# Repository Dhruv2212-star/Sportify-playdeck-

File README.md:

# Description- this project was made for controling any media sounds via the spotify playdeck without reopening the application on your desktop  

## The main components required for this build are 
1. mechenical keyboard switches X4 
2. seeed studio XIAO RP2040 X1
3. 0.91 Inch OLED Display X1

## Final schematic should be as following- 

# Update the schematic to PCB and Route the traces 

And once the traces and connections are made, create a rectangle and make sure all the components fit insite it.
IMPORTANT- the rectangle property should be set to "edge.cuts".

# Create the case 

## Bottom case 

## top case  

# ASSEMBELED FILE
this is an model of what your project will look life later 

# you can download all the file from the 'productions' folder 
this way you would escape the trouble of recreating the PCB the case for it and you can build it yourself!!  
Now once you have the files ready, Order the PCB and 3D print the case files  
solder all the components in their places   
hot glue the pcb in the case for extra strength  
# Schematic building 
1. Add these 3 components first-
-MODULE-SEEDUINO-XIAO
-sw_push
-PinHeader_1x04_P2.54mm_Vertical
2. Connect each Sw_push to their own gpio pin, i connected them to D0, D1, D2, D3
3. connect the other part of the Sw_push to Gnd port on the Xiao RP2040  
 **That's it for your switches! now for the LCD**  
4. now on 'PinHeader_1x04_P2.54mm_Vertical' connect pin 1 to GND on the XIAO RP2040, pin2- 3.3v, pin3- D5(SCL), pin4- D4(SDA)
**That's your schematic completed!**  
# PCB tracing
1. select update to PCB
2. select the footprints for each components
3. now click on one trace of the component's pad, this will show you where it supposed to be connected, draw the lines to that region
4. now do this for all the pads present on the PCB and traces them on the PCB  
   **Thats the PCB done!**
# Case 
## Note down the dimesions from the PCB model and start with a simple sketch of a box with your dimentions and, then make the walls to fit the PCB inside then make the top case from the dimensions of the bottom case you just made and cut out the parts you need to from the top case 
# Firmware flashing 
## instal circuitpython   
1. connect your microcontroler to your PC   
2. new drive called RPI-RP2 will appear    
3. paste "adafruit-circuitpython-seeeduino_xiao_rp2040-en_US-10.2.1" file from the 'Firmware' folder given    
4. The board automatically restarts  
5. the drive is now named 'CIRCUITPY'  
6. delete any file named 'code.py' in the CIRCUITPY drive if any  
7. now copy and past these files from the firmware folder  
8. "boot.py", "code.py", entire "lib" folder  
9. yout board should look like this

CIRCUITPY/  

boot.py  

code.py  

lib/  
10. save and close the window and boot it  
# That's it! 
## open spotify and now you can control the pause, play, next, previous funtions without opening your spotify desktop application 

Ai ussage- ai was used to select the correct liberaries for the code and also trouble shooting the schematic. that's it

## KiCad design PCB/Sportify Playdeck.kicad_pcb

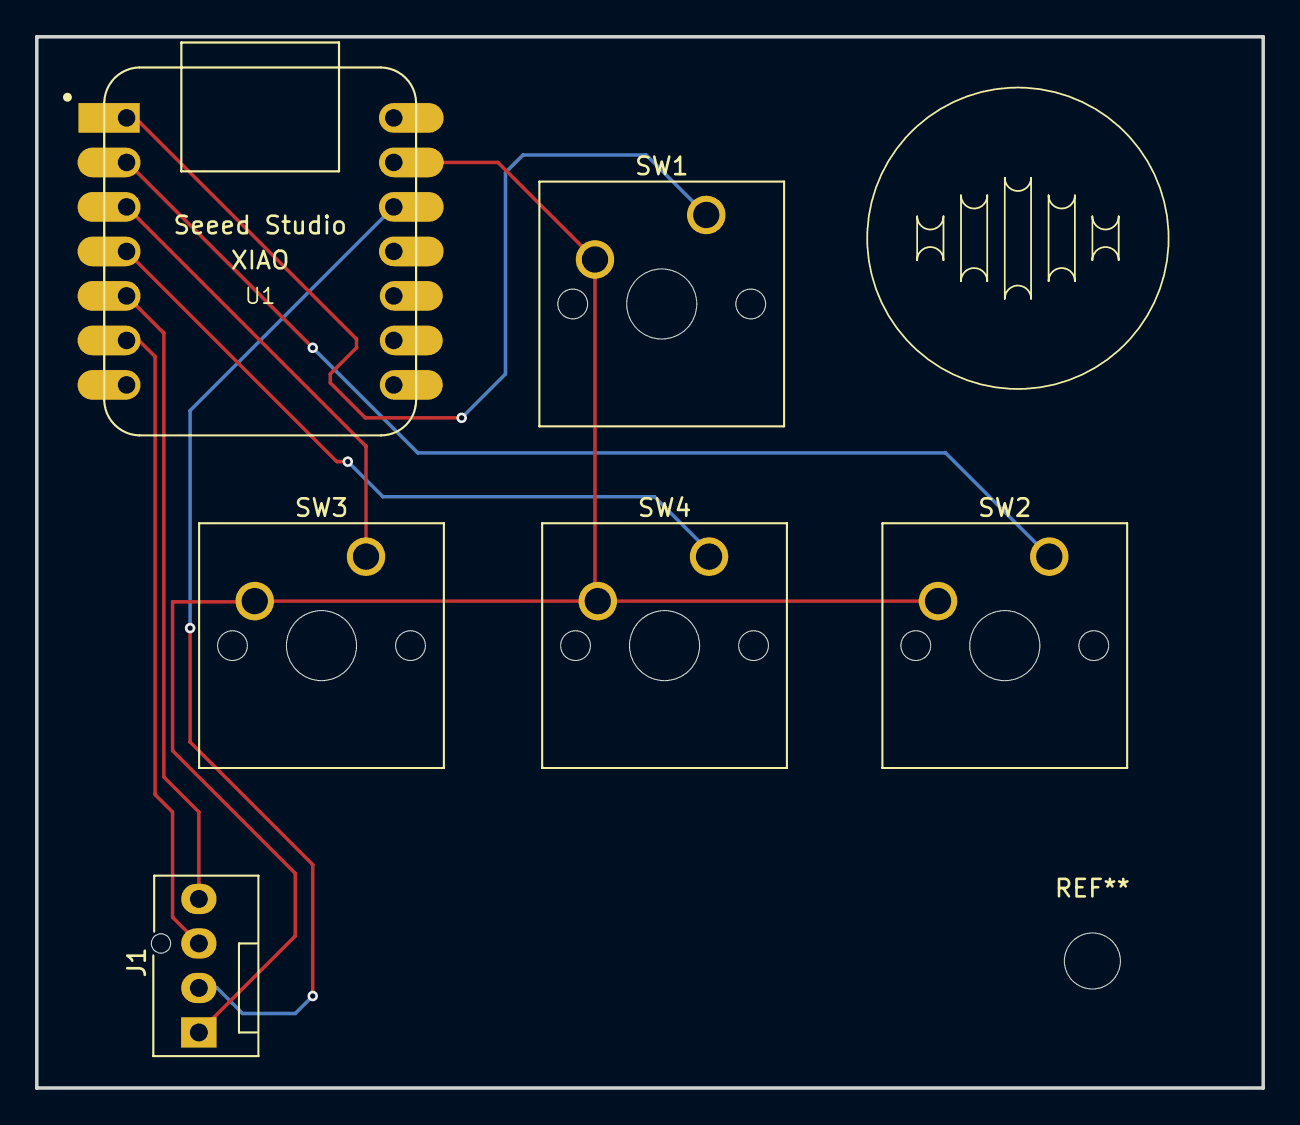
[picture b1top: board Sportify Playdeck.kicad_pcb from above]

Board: 2 copper layers, 70.0 x 60.0 mm, 6 parts (0 on the bottom side), 8 nets.

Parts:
J1: Conn_01x04_Pin; FanPinHeader_1x04_P2.54mm_Vertical
SW1, SW2, SW3, SW4: SW_Push; SW_Cherry_MX_1.00u_PCB
U1: MOUDLE-SEEEDUINO-XIAO; XIAO-Generic-Hybrid-14P-2.54-21X17.8MM

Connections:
unnamed: J1.1, SW1.2, SW2.2, SW3.2, SW4.2, U1.13 (GND)
unnamed: J1.2, U1.12 (3V3)
unnamed: J1.3, U1.6 (PA9_A5_D5_SCL)
unnamed: J1.4, U1.5 (PA8_A4_D4_SDA)
unnamed: SW1.1, U1.1 (PA02_A0_D0)
unnamed: SW2.1, U1.2 (PA4_A1_D1)
unnamed: SW3.1, U1.3 (PA10_A2_D2)
unnamed: SW4.1, U1.4 (PA11_A3_D3)
